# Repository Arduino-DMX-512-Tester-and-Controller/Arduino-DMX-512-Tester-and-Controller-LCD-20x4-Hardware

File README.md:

# **Arduino DMX-512 Tester and Controller**

## **Hardware - LCD 20x4**

***

Herramienta Open Hardware, para pruebas y control de iluminación de espectáculos a través del protocolo [DMX-512](http://es.wikipedia.org/wiki/Digital_Multiplex), ideal para hacer pruebas rápidas en instalaciones fijas o temporales de iluminación, sin la necesidad de instalar consolas de iluminación, interfaces o computadoras en ambientes al intemperie, hostiles o de difícil acceso.

***

Mas informacion en la Wiki

***

### **Basado en:**

- [Arduino Mega 2560 Rev-3](http://www.arduino.cc/en/Main/ArduinoBoardMega2560)
- [Librería Arduino cuatro universos DMX v0.3 - Deskontrol](http://www.deskontrol.net/blog/libreria-arduino-cuatro-universos-dmx/)
- [Libreria LCD v1.2.1 - Francisco Malpartida](https://bitbucket.org/fmalpartida/new-liquidcrystal/wiki/Home)
- [Simulación en Proteus de Arduino - Microcontrolandos](http://microcontrolandos.blogspot.mx/2012/12/arduino-componentes-para-o-proteus.html)
- [Encoder](http://www.robodosis.net/2013/01/encoder-rotativo-mecanico-con-pic16f877a_2.html)

***

- Esquemático y PCB en Proteus v8.0 SP1
- LCD de 4x20 con backlight y contraste controlado por software
- Alimentación desde USB, baterías o fuente de alimentación externa
- Encoder para navegacion entre menu
- Teclado numérico 4x4
- Interruptor de on/off
- Salida DMX desde bornera, XLR de 3 pin y XLR de 5 pin
- Leds de estado de salida DMX
- Simulación en Proteus v7.7 SP2 y v8.0 SP1
- Esquemático y PCB en Proteus v8.0 SP1
- Aclarar que para este proyecto se utilizó un Arduino Mega hecho en China
- Regulador para fuente externa, el arduino se calienta
- Bornera para salida de fuente regulada de 5V para uso general
- Led para salida de fuente regulada
- Botón de reset
- Opto acoplado a salida de dmx
- Convertidor de DC/DC para aislamiento de DMX
- SW de palanca para invertir polaridad de salida de DMX
- Jumper default eeprom en pin 9
- Driver para luz led como lampara
- SW para Key Light
- SW para Ext Light
- Espaciadores para fijación
- Leyendas de conexión
- Fuente externa, el arduino se calentaba

***

### 

- AGREGADO   - los bordes para la union del acrílico
- ELIMINADO  - base de teclado, queda sobre el acrílico
- AGREGADO   - jack de DC para alimentacion
- AGREGADO   - tornillo entre los conectores para agregar soporte
- CORREGIDO  - bornera de voltaje lateral metera mas
- CORREGIDO  - posición de SW esta al revés, cambiar leyenda en pcb

***

### 

- Simulacion en Proteus v7.7 SP2
- Librerias:
  - Arduino: https://geekelectronica.com/simular-arduino-con-proteus/
- Firmware v1.8 a v2.2

***

### **Simulador**

- Hardware v0.6 to v0.8
- Firmware v1.6 to v2.2

***

### **Esquematico**

***

### **PCB**

***

### **Simulador**

***

## **Licenciamiento:**

[Open Source Hardware (OSHW) v1.0](https://github.com/Arduino-DMX-512-Tester-and-Controller/Arduino-DMX-512-Tester-and-Controller-LCD-20x4-Hardware/blob/master/LICENCE.md)

***

## **Autor:**

- Daniel Becerril
- Copyright (C) 2015

***

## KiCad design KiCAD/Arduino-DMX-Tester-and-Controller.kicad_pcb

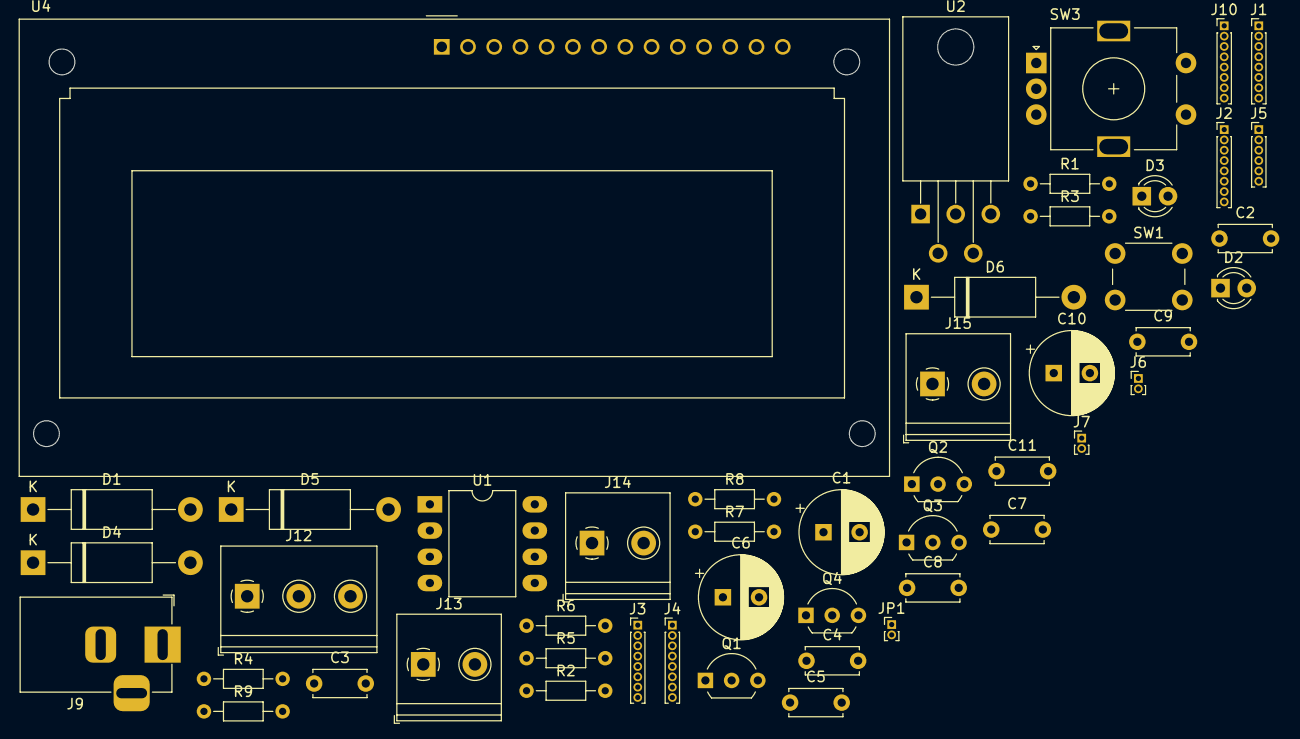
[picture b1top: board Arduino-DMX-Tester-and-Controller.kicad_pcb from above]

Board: 2 copper layers, 49 parts (0 on the bottom side), 44 nets, no tracks yet.

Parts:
C1: 100uF/63V; CP_Radial_D8.0mm_P3.50mm
C2, C3, C4, C5, C7, C8, C9, C11: 1nF; C_Disc_D5.0mm_W2.5mm_P5.00mm
C6: 330uF/16V; CP_Radial_D8.0mm_P3.50mm
C10: 47uF/16V; CP_Radial_D8.0mm_P3.50mm
D1, D4, D5: 1N4001; D_DO-15_P15.24mm_Horizontal
D2, D3: LED; LED_D3.0mm
D6: 1N5819; D_DO-15_P15.24mm_Horizontal
J1, J2, J3, J4, J10: Pin Header 8; PinHeader_1x08_P1.00mm_Vertical
J5: Pin Header 6; PinHeader_1x06_P1.00mm_Vertical
J6, J7: Pin Header 2; PinHeader_1x02_P1.00mm_Vertical
J9: Jack-DC; BarrelJack_Horizontal
J12: Terminal Screw 3; TerminalBlock_Philmore_TB133_1x03_P5.00mm_Horizontal
J13, J14, J15: Terminal Screw 2; TerminalBlock_Philmore_TB132_1x02_P5.00mm_Horizontal
JP1: Jumper; PinHeader_1x02_P1.00mm_Vertical
Q1, Q2, Q4: 2N2222; TO-92L_Inline_Wide
Q3: BC548; TO-92L_Inline_Wide
R1, R3: 330; R_Axial_DIN0204_L3.6mm_D1.6mm_P7.62mm_Horizontal
R2: 120; R_Axial_DIN0204_L3.6mm_D1.6mm_P7.62mm_Horizontal
R4, R5, R7: 1K; R_Axial_DIN0204_L3.6mm_D1.6mm_P7.62mm_Horizontal
R6, R8: 22K; R_Axial_DIN0204_L3.6mm_D1.6mm_P7.62mm_Horizontal
R9: 680; R_Axial_DIN0204_L3.6mm_D1.6mm_P7.62mm_Horizontal
SW1: Micro Switch; SW_PUSH_6mm
SW3: Encoder; RotaryEncoder_Alps_EC11E-Switch_Vertical_H20mm
U1: MAX485E; DIP-8_W10.16mm_LongPads
U2: LM2575-5.0BT; TO-220-5_P3.4x3.8mm_StaggerEven_Lead7.13mm_TabDown
U4: NHD-0420H1Z; LM16255

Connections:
+5V: C2.2, C3.2, C4.2, C5.2, C7.2, C8.2, C9.2, C11.2, J1.4, J7.1, J7.2, J14.1, J15.1, R1.2, R8.2, U1.1, U1.2, U1.3, U1.8, U4.2
DMX_Out: J3.2, U1.4
Enc_A: C8.1, J3.7, SW3.A
Enc_B: C7.1, J3.8, SW3.B
Enc_C: C9.1, J2.1, SW3.S1
GNDREF: C1.2, C6.2, C10.2, C11.1, D6.2, J1.2, J1.3, J6.1, J6.2, J9.2, J12.1, JP1.2, Q1.1, Q2.1, Q3.3, Q4.1, R3.1, SW1.2, SW3.C, SW3.S2, U1.5, U2.3, U2.5, U4.1, U4.5, U4.7, U4.8, U4.9, U4.10
Key_Light: J2.4, R4.1
LCD_BL: J2.6, R5.1
LCD_Cont: J2.5, R6.1
LCD_Contrast: C10.1, R9.2, U4.3
LCD_D4: J5.4, U4.11
LCD_D5: J5.3, U4.12
LCD_D6: J5.2, U4.13
LCD_D7: J5.1, U4.14
LCD_E: J5.5, U4.6
LCD_RS: J5.6, U4.4
Light: J2.3, R7.1
unnamed: C1.1, D1.1, U2.1
unnamed: C6.1, U2.4
unnamed: D1.2, J9.1
unnamed: D2.1, D4.2, R2.2
unnamed: D2.2, R1.1
unnamed: D3.1, R3.2
unnamed: D3.2, D5.1, R2.1
unnamed: D4.1, U1.7
unnamed: D5.2, U1.6
unnamed: D6.1, U2.2
unnamed: J1.6, SW1.1
unnamed: J2.2, JP1.1
unnamed: J14.2, Q1.3
unnamed: J15.2, Q4.3
unnamed: Q1.2, R4.2
unnamed: Q2.2, R5.2
unnamed: Q3.1, R8.1, R9.1
unnamed: Q3.2, R6.2
unnamed: Q4.2, R7.2
Num_1: C2.1, J4.4, J10.5
Num_2: C3.1, J4.3, J10.6
Num_3: C4.1, J4.2, J10.7
Num_4: C5.1, J4.1, J10.8
Num_A: J4.8, J10.1
Num_B: J4.7, J10.2
Num_C: J4.6, J10.3
Num_D: J4.5, J10.4

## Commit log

2020-07-31 v0.0 - update
2020-07-31 Orden
2020-07-31 update imagenes
2020-07-31 Update - Documentacion
2020-07-31 update
    se quitaron los temporales de proteus y se agrego la importacion del simulador a v8.0
2020-07-31 remplazo de archivo de proteus a v0.1
2020-07-31 Archivo de proteus actualizado a v8.2
2020-07-31 actualizacion de imagenes para README
2020-07-31 agregado captura del simulador
2020-07-31 Update DMX Controller - Proteus 80.pdsprj
    v8.2
2020-08-01 archivo de proteus a v8.2
2020-08-01 capturas actualizadas
2020-08-01 agregado pdf de preprensa
2020-08-01 agregado fotos de armado
2020-08-01 Simulador actualizado
2020-08-01 Agregados carpeta de logos y social
2020-08-01 Esquematico y pcb capturas
2020-08-01 fotos de armado eliminadas
2020-08-01 PDFs generados
2020-08-01 Documentacion update
2020-08-01 PDFs, proyeus a v8.2
2020-08-01 media update, sumulador update
2020-08-01 Simulador en v80
2020-08-01 media update
2020-08-01 update docs
2020-08-01 PCB media update
2020-08-01 Set theme jekyll-theme-slate
2020-08-01 archivo de proteus firmato v8.21
2020-08-02 icon update
2020-08-02 wiki icon update

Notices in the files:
README.md:
License: OSHW v1.0
